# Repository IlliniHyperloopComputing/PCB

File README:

# Illini Hyperloop PCB

The shared development environment for the Illini Hyperloop PCB team. Contains all libraries and schematics for the electronics on the pod. 

## Getting Started

Obtain full student copy of Eagle. https://www.autodesk.com/education/free-software/eagle
Initialize repository in a Eagle folder. 
After youve got your git repository up and running youre going to want to configure eagle. Files included in the library folder arent enabled by default. Youre going to have to go through and make sure you select Use All for the subfolders provided so the little green dot appears to the right side next to libraries in the Control Panel.

### Prerequisites

Eagle 

## Authors

* **Matthew Klock** - *Team Lead* - [Matthew-Klock](https://github.com/Matthew-Klock)

See also the list of [contributors](https://github.com/your/project/contributors) who participated in this project.

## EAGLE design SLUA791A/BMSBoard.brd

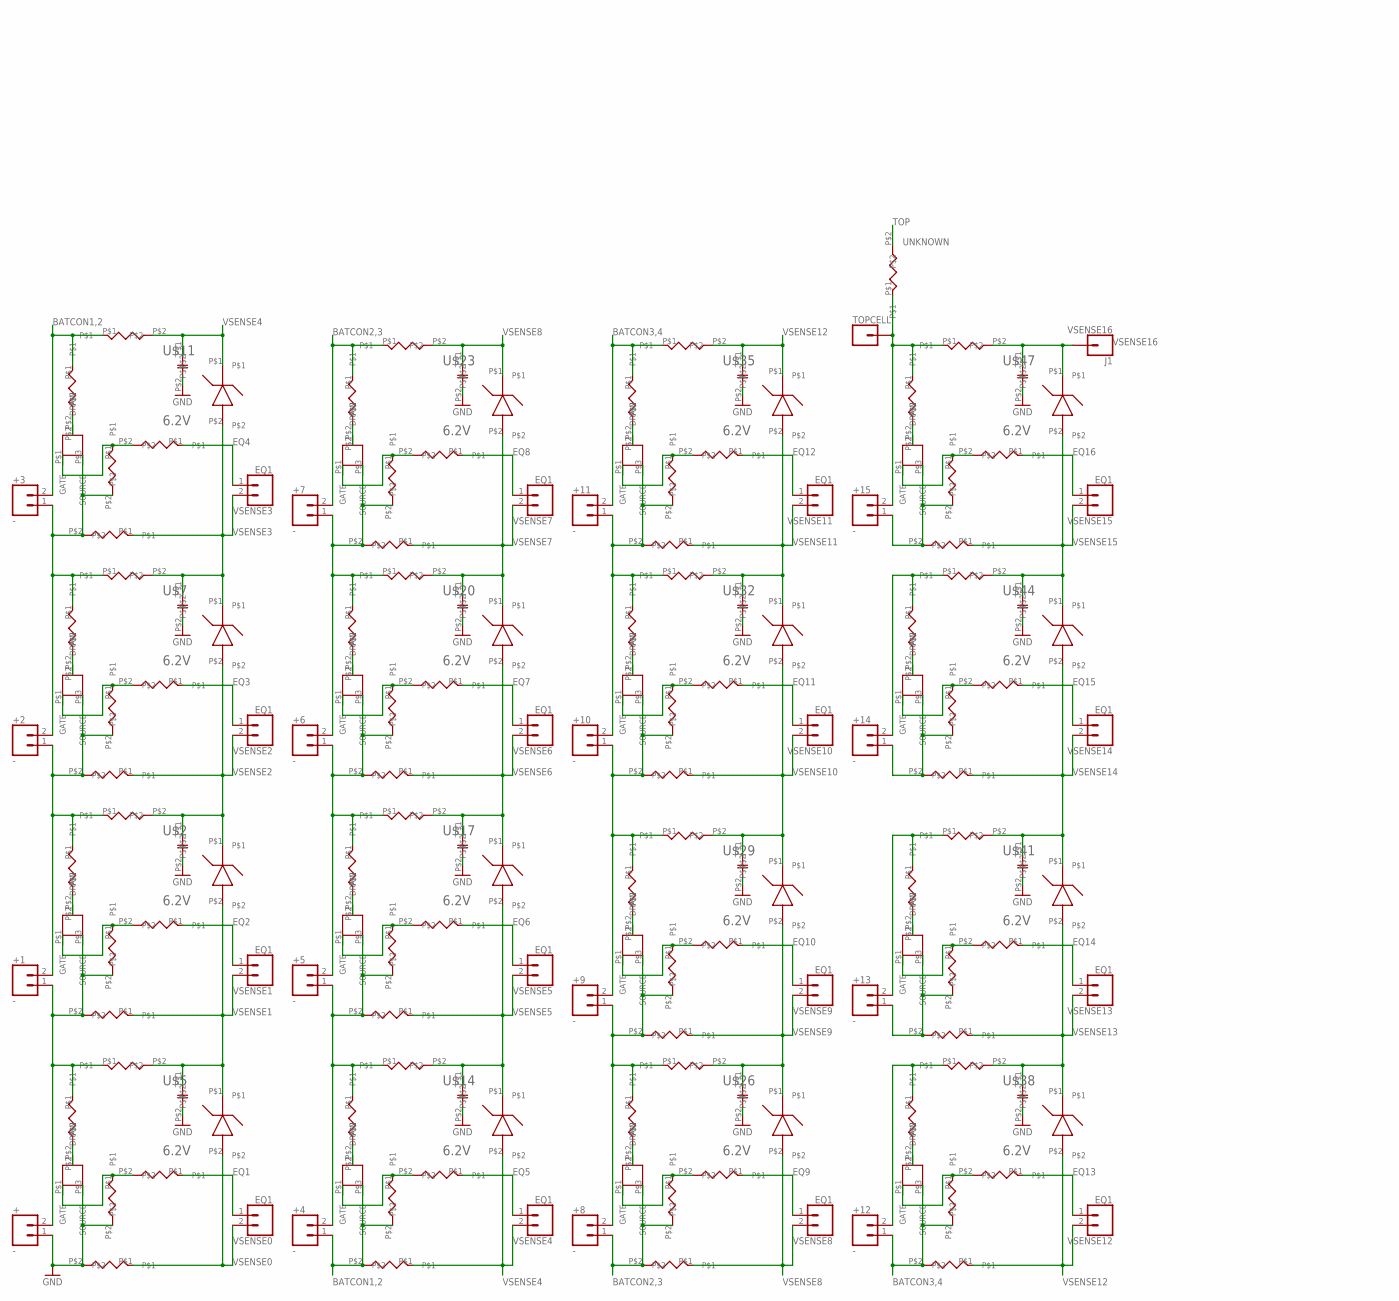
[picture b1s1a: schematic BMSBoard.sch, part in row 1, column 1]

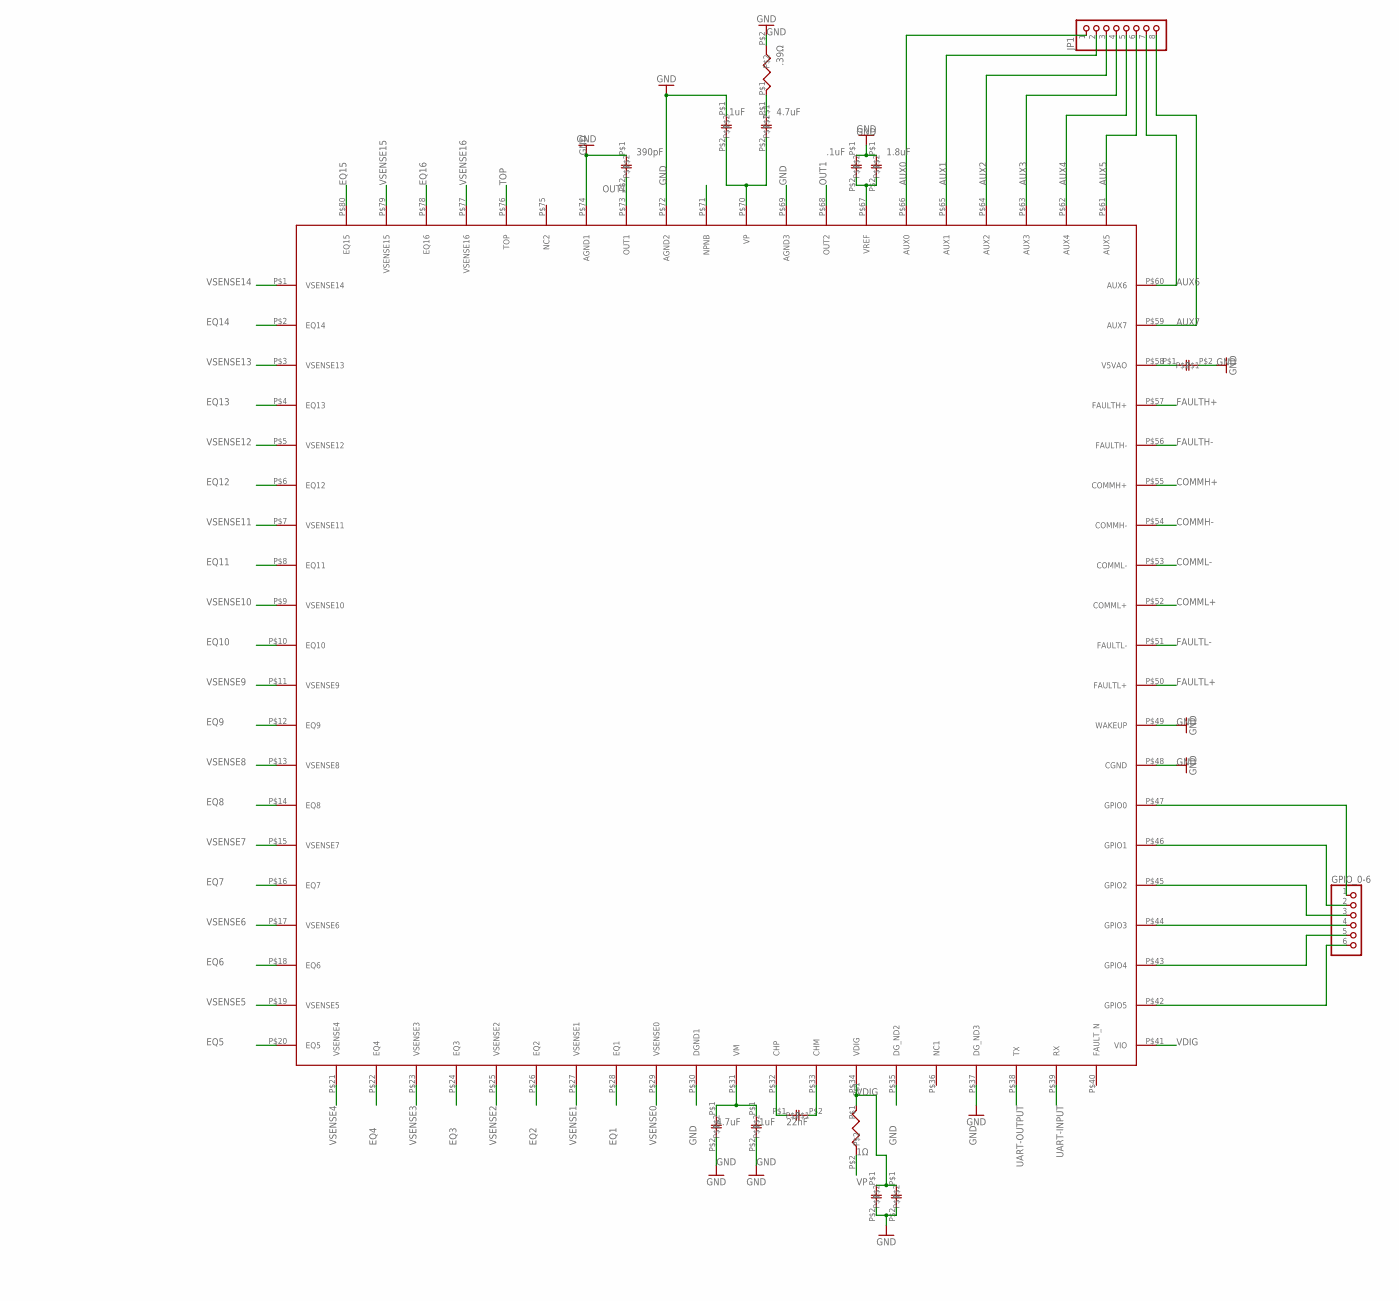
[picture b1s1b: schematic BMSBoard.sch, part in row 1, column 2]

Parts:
1UF, 1UF1, 1UF2, 1UF3, 1UF4, 1UF5, 1UF6, 1UF7, 1UF8, 1UF9, 1UF10, 1UF11, 1UF12, 1UF13, 1UF14, 1UF15: 1uF; CL21B105KBFNNNG
2KΩ, 2KΩ1, 2KΩ2, 2KΩ3, 2KΩ4, 2KΩ5, 2KΩ6, 2KΩ7, 2KΩ8, 2KΩ9, 2KΩ10, 2KΩ11, 2KΩ12, 2KΩ13, 2KΩ14, 2KΩ15: 2kΩ; PWR3014W1000JE
75Ω, 75Ω1, 75Ω2, 75Ω3, 75Ω4, 75Ω5, 75Ω6, 75Ω7, 75Ω8, 75Ω9, 75Ω10, 75Ω11, 75Ω12, 75Ω13, 75Ω14, 75Ω15: 75Ω; PWR3014W1000JE
100KΩ, 100KΩ1, 100KΩ2, 100KΩ3, 100KΩ4, 100KΩ5, 100KΩ6, 100KΩ7, 100KΩ8, 100KΩ9, 100KΩ10, 100KΩ11, 100KΩ12, 100KΩ13, 100KΩ14, 100KΩ15: 100kΩ; PWR3014W1000JE
100Ω, 100Ω1, 100Ω2, 100Ω3, 100Ω4, 100Ω5, 100Ω6, 100Ω7, 100Ω8, 100Ω9, 100Ω10, 100Ω11, 100Ω12, 100Ω13, 100Ω14, 100Ω15: 100Ω; PWR3014W1000JE
+, +1, +2, +3, +4, +5, +6, +7, +8, +9, +10, +11, +12, +13, +14, +15: -; 1X02
GPIO_0-6: PINHD-1X6; 1X06
J1: VSENSE16; 1X01
JP1: PINHD-1X8BIG; 1X08-BIG
TOPCELL: CONN_01; 1X01
U$1, U$4, U$6, U$10, U$13, U$16, U$19, U$22, U$25, U$28, U$31, U$34, U$37, U$40, U$43, U$46: 2V7002KT1G
U$2, U$5, U$7, U$11, U$14, U$17, U$20, U$23, U$26, U$29, U$32, U$35, U$38, U$41, U$44, U$47: 6.2V; SOD-123-2
U$3, U$8, U$9, U$12, U$15, U$18, U$21, U$24, U$27, U$30, U$33, U$36, U$39, U$42, U$45, U$48: 100Ω; PWR3014W1000JE
U$49: BQ76PL455A-Q1
U$50: 22nF; CL21B105KBFNNNG
U$51, U$52, U$54, U$55, U$56, U$57, U$58, U$59, U$60, U$61: CL21B105KBFNNNG
U$53: 1Ω; PWR3014W1000JE
U$62, U$63: PWR3014W1000JE
VSENSE0, VSENSE1, VSENSE2, VSENSE3, VSENSE4, VSENSE5, VSENSE6, VSENSE7, VSENSE8, VSENSE9, VSENSE10, VSENSE11, VSENSE12, VSENSE13, VSENSE14, VSENSE15: EQ1; 1X02

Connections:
AUX0: JP1.1, U$49.P$66 (AUX0)
AUX1: JP1.2, U$49.P$65 (AUX1)
AUX2: JP1.3, U$49.P$64 (AUX2)
AUX3: JP1.4, U$49.P$63 (AUX3)
AUX4: JP1.5, U$49.P$62 (AUX4)
AUX5: JP1.6, U$49.P$61 (AUX5)
AUX6: JP1.7, U$49.P$60 (AUX6)
AUX7: JP1.8, U$49.P$59 (AUX7)
BATCON1,2: 75Ω3.P$1, 100KΩ4.P$2, 100Ω4.P$2, +3.2, +4.1, U$12.P$1, U$13.P$3 (SOURCE)
BATCON2,3: 75Ω7.P$1, 100KΩ8.P$2, 100Ω8.P$2, +7.2, +8.1, U$24.P$1, U$25.P$3 (SOURCE)
BATCON3,4: 75Ω11.P$1, 100KΩ12.P$2, 100Ω12.P$2, +11.2, +12.1, U$36.P$1, U$37.P$3 (SOURCE)
COMMH+: U$49.P$55 (COMMH+)
COMMH-: U$49.P$54 (COMMH-)
COMML+: U$49.P$52 (COMML+)
COMML-: U$49.P$53 (COMML-)
EQ1: 2KΩ.P$1, U$49.P$28 (EQ1), VSENSE0.1
EQ2: 2KΩ1.P$1, U$49.P$26 (EQ2), VSENSE1.1
EQ3: 2KΩ2.P$1, U$49.P$24 (EQ3), VSENSE2.1
EQ4: 2KΩ3.P$1, U$49.P$22 (EQ4), VSENSE3.1
EQ5: 2KΩ4.P$1, U$49.P$20 (EQ5), VSENSE4.1
EQ6: 2KΩ5.P$1, U$49.P$18 (EQ6), VSENSE5.1
EQ7: 2KΩ6.P$1, U$49.P$16 (EQ7), VSENSE6.1
EQ8: 2KΩ7.P$1, U$49.P$14 (EQ8), VSENSE7.1
EQ9: 2KΩ8.P$1, U$49.P$12 (EQ9), VSENSE8.1
EQ10: 2KΩ9.P$1, U$49.P$10 (EQ10), VSENSE9.1
EQ11: 2KΩ10.P$1, U$49.P$8 (EQ11), VSENSE10.1
EQ12: 2KΩ11.P$1, U$49.P$6 (EQ12), VSENSE11.1
EQ13: 2KΩ12.P$1, U$49.P$4 (EQ13), VSENSE12.1
EQ14: 2KΩ13.P$1, U$49.P$2 (EQ14), VSENSE13.1
EQ15: 2KΩ14.P$1, U$49.P$80 (EQ15), VSENSE14.1
EQ16: 2KΩ15.P$1, U$49.P$78 (EQ16), VSENSE15.1
FAULTH+: U$49.P$57 (FAULTH+)
FAULTH-: U$49.P$56 (FAULTH-)
FAULTL+: U$49.P$50 (FAULTL+)
FAULTL-: U$49.P$51 (FAULTL-)
GND: 1UF.P$2, 1UF1.P$2, 1UF2.P$2, 1UF3.P$2, 1UF4.P$2, 1UF5.P$2, 1UF6.P$2, 1UF7.P$2, 1UF8.P$2, 1UF9.P$2, 1UF10.P$2, 1UF11.P$2, 1UF12.P$2, 1UF13.P$2, 1UF14.P$2, 1UF15.P$2, 100KΩ.P$2, 100Ω.P$2, +.1, U$4.P$3 (SOURCE), U$49.P$30 (DGND1), U$49.P$35 (DG_ND2), U$49.P$37 (DG_ND3), U$49.P$48 (CGND), U$49.P$49 (WAKEUP), U$49.P$69 (AGND3), U$49.P$72 (AGND2), U$49.P$74 (AGND1), U$51.P$2, U$52.P$2, U$54.P$2, U$55.P$2, U$56.P$2, U$57.P$1, U$58.P$1, U$59.P$1, U$60.P$1, U$62.P$2
unnamed: 2KΩ.P$2, 100KΩ.P$1, U$4.P$1 (GATE)
unnamed: U$61.P$1, U$62.P$1
unnamed: 75Ω.P$2, U$4.P$2 (DRAIN)
unnamed: 75Ω.P$1, 100KΩ1.P$2, 100Ω1.P$2, +.2, +1.1, U$1.P$3 (SOURCE), U$8.P$1
unnamed: 75Ω2.P$1, 100KΩ3.P$2, 100Ω3.P$2, +2.2, +3.1, U$9.P$1, U$10.P$3 (SOURCE)
unnamed: 2KΩ1.P$2, 100KΩ1.P$1, U$1.P$1 (GATE)
unnamed: 75Ω1.P$2, U$1.P$2 (DRAIN)
unnamed: 75Ω1.P$1, 100KΩ2.P$2, 100Ω2.P$2, +1.2, +2.1, U$3.P$1, U$6.P$3 (SOURCE)
unnamed: 2KΩ2.P$2, 100KΩ2.P$1, U$6.P$1 (GATE)
unnamed: 75Ω2.P$2, U$6.P$2 (DRAIN)
unnamed: 2KΩ3.P$2, 100KΩ3.P$1, U$10.P$1 (GATE)
unnamed: 75Ω3.P$2, U$10.P$2 (DRAIN)
unnamed: 2KΩ4.P$2, 100KΩ4.P$1, U$13.P$1 (GATE)
unnamed: 75Ω4.P$2, U$13.P$2 (DRAIN)
unnamed: 2KΩ5.P$2, 100KΩ5.P$1, U$16.P$1 (GATE)
unnamed: 75Ω5.P$2, U$16.P$2 (DRAIN)
unnamed: 75Ω5.P$1, 100KΩ6.P$2, 100Ω6.P$2, +5.2, +6.1, U$18.P$1, U$19.P$3 (SOURCE)
unnamed: 2KΩ6.P$2, 100KΩ6.P$1, U$19.P$1 (GATE)
unnamed: 75Ω6.P$2, U$19.P$2 (DRAIN)
unnamed: 2KΩ7.P$2, 100KΩ7.P$1, U$22.P$1 (GATE)
unnamed: 75Ω7.P$2, U$22.P$2 (DRAIN)
unnamed: 2KΩ8.P$2, 100KΩ8.P$1, U$25.P$1 (GATE)
unnamed: 75Ω8.P$2, U$25.P$2 (DRAIN)
unnamed: 75Ω8.P$1, 100KΩ9.P$2, 100Ω9.P$2, +8.2, +9.1, U$27.P$1, U$28.P$3 (SOURCE)
unnamed: 2KΩ9.P$2, 100KΩ9.P$1, U$28.P$1 (GATE)
unnamed: 75Ω9.P$2, U$28.P$2 (DRAIN)
unnamed: 75Ω9.P$1, 100KΩ10.P$2, 100Ω10.P$2, +9.2, +10.1, U$30.P$1, U$31.P$3 (SOURCE)
unnamed: 2KΩ10.P$2, 100KΩ10.P$1, U$31.P$1 (GATE)
unnamed: 75Ω10.P$2, U$31.P$2 (DRAIN)
unnamed: 2KΩ11.P$2, 100KΩ11.P$1, U$34.P$1 (GATE)
unnamed: 75Ω11.P$2, U$34.P$2 (DRAIN)
unnamed: 2KΩ12.P$2, 100KΩ12.P$1, U$37.P$1 (GATE)
unnamed: 75Ω12.P$2, U$37.P$2 (DRAIN)
unnamed: 75Ω12.P$1, +12.2, U$39.P$1
unnamed: 2KΩ13.P$2, 100KΩ13.P$1, U$40.P$1 (GATE)
unnamed: 75Ω13.P$2, U$40.P$2 (DRAIN)
unnamed: 75Ω13.P$1, +13.2, U$42.P$1
unnamed: 2KΩ14.P$2, 100KΩ14.P$1, U$43.P$1 (GATE)
unnamed: 75Ω14.P$2, U$43.P$2 (DRAIN)
unnamed: 75Ω14.P$1, +14.2, U$45.P$1
unnamed: 2KΩ15.P$2, 100KΩ15.P$1, U$46.P$1 (GATE)
unnamed: 75Ω15.P$2, U$46.P$2 (DRAIN)
unnamed: 75Ω15.P$1, +15.2, TOPCELL.1, U$48.P$1, U$63.P$1
unnamed: 75Ω4.P$1, 100KΩ5.P$2, 100Ω5.P$2, +4.2, +5.1, U$15.P$1, U$16.P$3 (SOURCE)
unnamed: 75Ω6.P$1, 100KΩ7.P$2, 100Ω7.P$2, +6.2, +7.1, U$21.P$1, U$22.P$3 (SOURCE)
unnamed: 75Ω10.P$1, 100KΩ11.P$2, 100Ω11.P$2, +10.2, +11.1, U$33.P$1, U$34.P$3 (SOURCE)
unnamed: 100KΩ13.P$2, 100Ω13.P$2, +13.1, U$40.P$3 (SOURCE)
unnamed: 100KΩ14.P$2, 100Ω14.P$2, +14.1, U$43.P$3 (SOURCE)
unnamed: 100KΩ15.P$2, 100Ω15.P$2, +15.1, U$46.P$3 (SOURCE)
unnamed: U$49.P$31 (VM), U$51.P$1, U$52.P$1
unnamed: U$49.P$32 (CHP), U$50.P$1
unnamed: U$49.P$33 (CHM), U$50.P$2
unnamed: GPIO_0-6.6, U$49.P$42 (GPIO5)
unnamed: GPIO_0-6.5, U$49.P$43 (GPIO4)
unnamed: GPIO_0-6.4, U$49.P$44 (GPIO3)
unnamed: GPIO_0-6.3, U$49.P$45 (GPIO2)
unnamed: GPIO_0-6.2, U$49.P$46 (GPIO1)
unnamed: GPIO_0-6.1, U$49.P$47 (GPIO0)
unnamed: U$49.P$58 (V5VAO), U$56.P$1
unnamed: U$49.P$70 (VP), U$60.P$2, U$61.P$2
OUT1: U$49.P$68 (OUT2), U$49.P$73 (OUT1), U$59.P$2
TOP: U$49.P$76 (TOP), U$63.P$2
UART-INPUT: U$49.P$39 (RX)
UART-OUTPUT: U$49.P$38 (TX)
VDIG: U$49.P$34 (VDIG), U$49.P$41 (VIO), U$53.P$1, U$54.P$1, U$55.P$1
VP: U$53.P$2
VREF: U$49.P$67 (VREF), U$57.P$2, U$58.P$2
VSENSE0: 100Ω.P$1, U$5.P$2, U$49.P$29 (VSENSE0), VSENSE0.2
VSENSE1: 1UF.P$1, 100Ω1.P$1, U$2.P$2, U$5.P$1, U$8.P$2, U$49.P$27 (VSENSE1), VSENSE1.2
VSENSE2: 1UF1.P$1, 100Ω2.P$1, U$2.P$1, U$3.P$2, U$7.P$2, U$49.P$25 (VSENSE2), VSENSE2.2
VSENSE3: 1UF2.P$1, 100Ω3.P$1, U$7.P$1, U$9.P$2, U$11.P$2, U$49.P$23 (VSENSE3), VSENSE3.2
VSENSE4: 1UF3.P$1, 100Ω4.P$1, U$11.P$1, U$12.P$2, U$14.P$2, U$49.P$21 (VSENSE4), VSENSE4.2
VSENSE5: 1UF4.P$1, 100Ω5.P$1, U$14.P$1, U$15.P$2, U$17.P$2, U$49.P$19 (VSENSE5), VSENSE5.2
VSENSE6: 1UF5.P$1, 100Ω6.P$1, U$17.P$1, U$18.P$2, U$20.P$2, U$49.P$17 (VSENSE6), VSENSE6.2
VSENSE7: 1UF6.P$1, 100Ω7.P$1, U$20.P$1, U$21.P$2, U$23.P$2, U$49.P$15 (VSENSE7), VSENSE7.2
VSENSE8: 1UF7.P$1, 100Ω8.P$1, U$23.P$1, U$24.P$2, U$26.P$2, U$49.P$13 (VSENSE8), VSENSE8.2
VSENSE9: 1UF8.P$1, 100Ω9.P$1, U$26.P$1, U$27.P$2, U$29.P$2, U$49.P$11 (VSENSE9), VSENSE9.2
VSENSE10: 1UF9.P$1, 100Ω10.P$1, U$29.P$1, U$30.P$2, U$32.P$2, U$49.P$9 (VSENSE10), VSENSE10.2
VSENSE11: 1UF10.P$1, 100Ω11.P$1, U$32.P$1, U$33.P$2, U$35.P$2, U$49.P$7 (VSENSE11), VSENSE11.2
VSENSE12: 1UF11.P$1, 100Ω12.P$1, U$35.P$1, U$36.P$2, U$38.P$2, U$49.P$5 (VSENSE12), VSENSE12.2
VSENSE13: 1UF12.P$1, 100Ω13.P$1, U$38.P$1, U$39.P$2, U$41.P$2, U$49.P$3 (VSENSE13), VSENSE13.2
VSENSE14: 1UF13.P$1, 100Ω14.P$1, U$41.P$1, U$42.P$2, U$44.P$2, U$49.P$1 (VSENSE14), VSENSE14.2
VSENSE15: 1UF14.P$1, 100Ω15.P$1, U$44.P$1, U$45.P$2, U$47.P$2, U$49.P$79 (VSENSE15), VSENSE15.2
VSENSE16: 1UF15.P$1, J1.1, U$47.P$1, U$48.P$2, U$49.P$77 (VSENSE16)

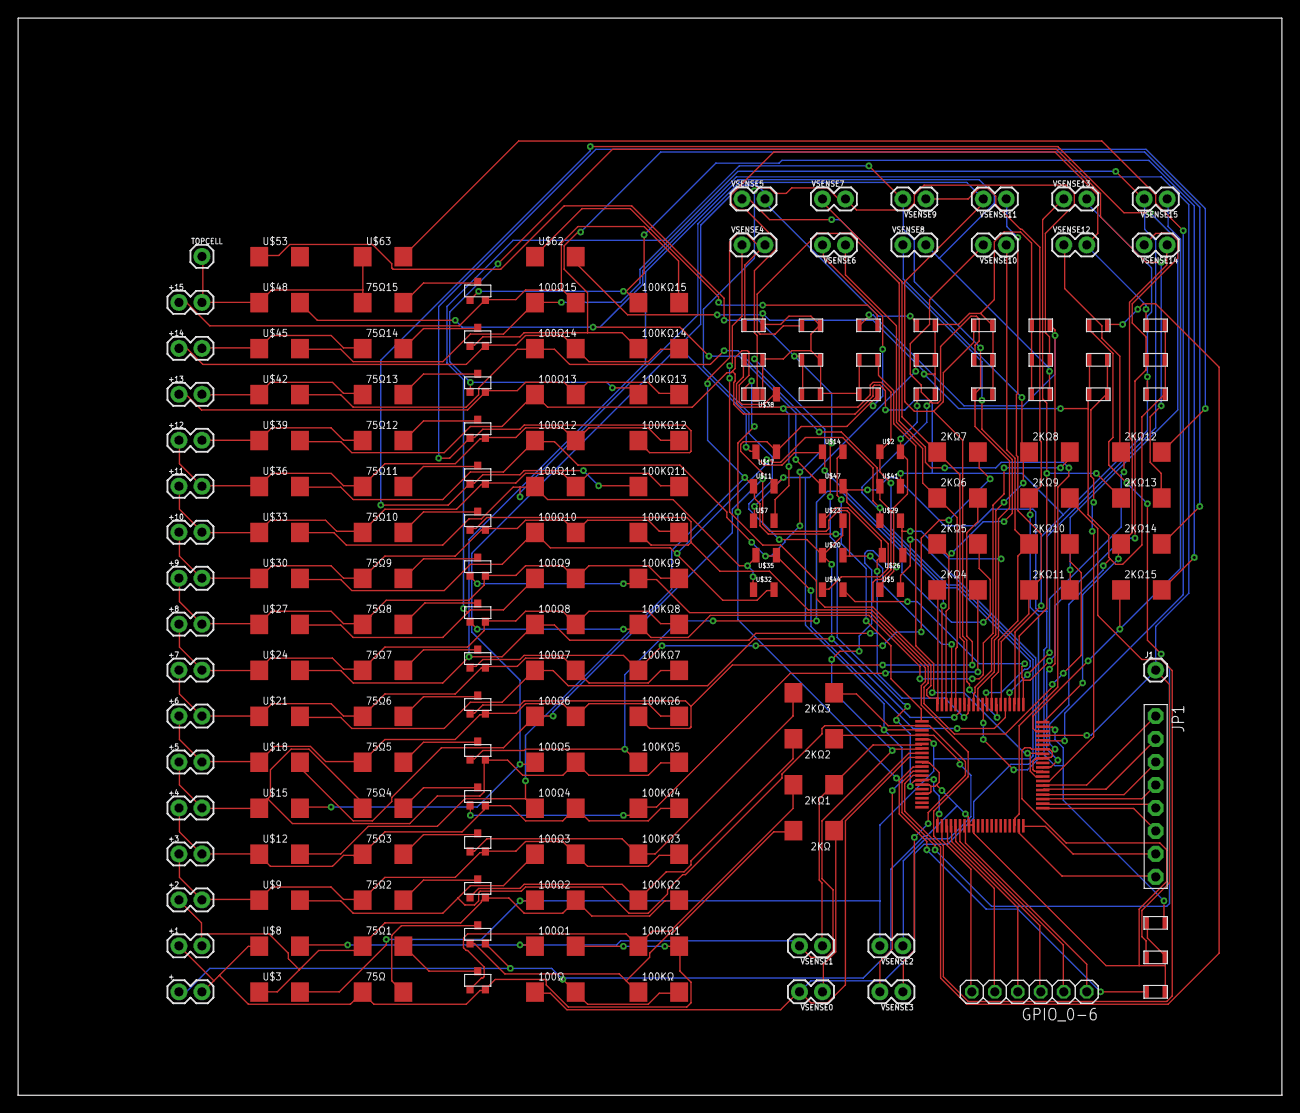
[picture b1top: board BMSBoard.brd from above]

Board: 2 copper layers, 139.7 x 119.0 mm, 179 parts (0 on the bottom side), 109 nets.

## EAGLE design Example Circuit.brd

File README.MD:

# Illini Hyperloop PCB

The shared development environment for the Illini Hyperloop PCB team. Contains all libraries and schematics for the electronics on the pod. 

## Repo layout:
1. Default branch is `pod4`, and pull requests must be made to merge into it
2. `master` branch will only be used for correct, working code. A pull request must be made to merge

## Getting Started

1. [Obtain full student copy of Eagle.](https://www.autodesk.com/education/free-software/eagle)
2. Clone this Repo: `git clone https://github.com/IlliniHyperloopComputing/PCB` 
3. Move inside the `PCB` folder that was just created. 
4. Run `git checkout -b *YOUR-NAME* `. This creates a branch for you to work on
5. Add the respective paths to libraries, boards, etc in EAGLE (Options>Directories).
6. Make your updates/ changes
7. `git status` to view changes, and use `git add *file* ` to add files, and then `git commit -m "your-message"`. 
8. `git push origin *YOUR-NAME* `. If there is an issue, do what `git` suggests you run, or it might be because you are not a member of our GitHub organization (Contact us).

### Prerequisites

* Eagle 

## Pull Requests
* Write a short description of what you did for the request.
* Please add your devices to Hyperloop-Library/Pod4.lbr, do not make them their own library.

## Authors

* **Matthew-Klock** - *Team Lead* - [Matthew Klock](https://github.com/Matthew-Klock)

See also the list of [team members](https://github.com/orgs/IlliniHyperloopComputing/teams/pcb-team) who participated in this project.

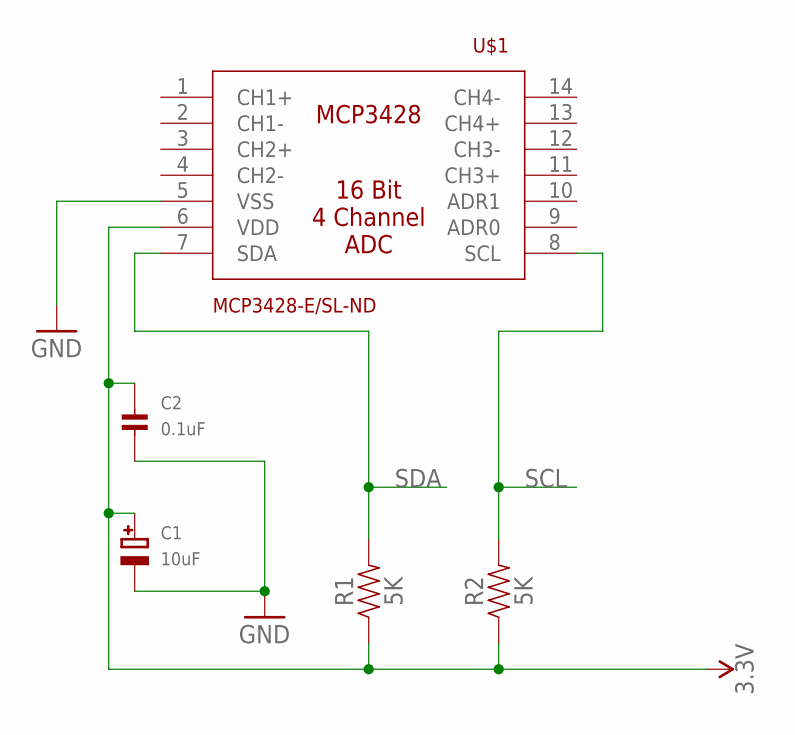
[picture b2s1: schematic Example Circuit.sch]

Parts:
C1: 10uF; EIA3216-18/A-R
C2: 0.1uF; 0603
R1, R2: 5K; 0603
U$1: MCP3428-E/SL-ND; 14SOIC

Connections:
3.3V: C1.+, C2.1, R1.1, R2.1, U$1.6 (VDD)
GND: C1.-, C2.2, U$1.5 (VSS)
SCL: R2.2, U$1.8 (SCL)
SDA: R1.2, U$1.7 (SDA)

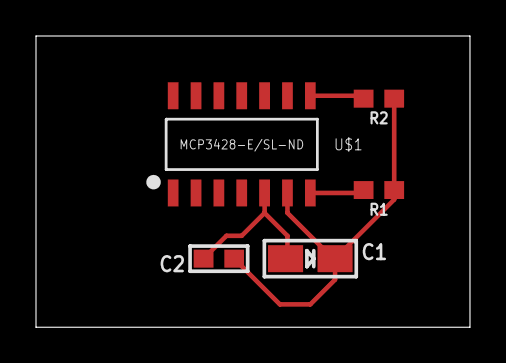
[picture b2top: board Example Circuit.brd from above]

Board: 2 copper layers, 24.1 x 16.2 mm, 5 parts (0 on the bottom side), 4 nets.

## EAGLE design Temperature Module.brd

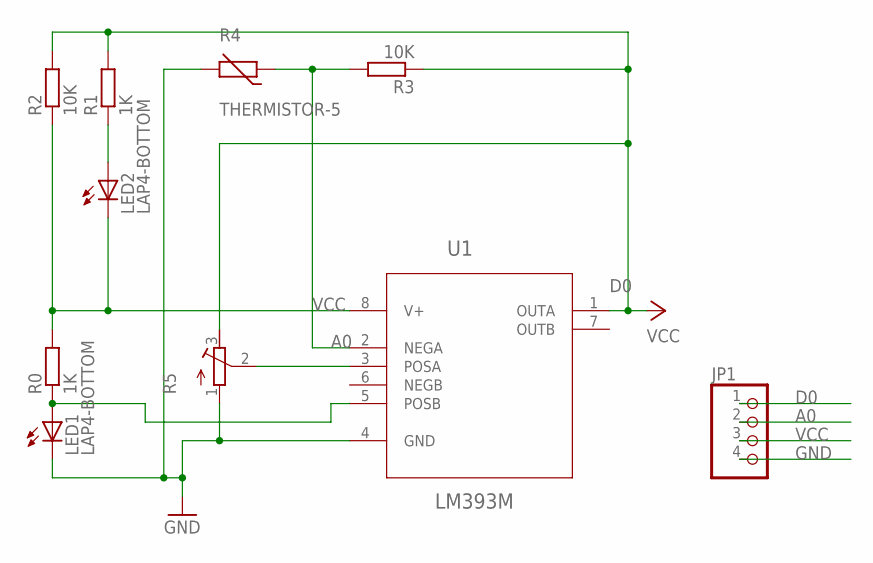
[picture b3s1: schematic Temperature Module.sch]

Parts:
JP1: PINHD-1X4; 1X04
LED1, LED2: LAP4-BOTTOM; P47F-BOTTOM
R0, R1: 1K; MINI_MELF-0207R
R2, R3: 10K; MINI_MELF-0207R
R4: THERMISTOR-5; R-5
R5: R-TRIMMCVR42A; RTRIMCVR42A
U1: LM393M; SOIC127P620X175-8N

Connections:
A0: JP1.2, R3.2, R4.1, U1.2 (NEGA)
D0: JP1.1, R1.2, R2.2, R3.1, R5.3 (E), U1.1 (OUTA)
GND: JP1.4, LED1.C, R4.2, R5.1 (A), U1.4 (GND)
unnamed: R5.2 (S), U1.3 (POSA)
unnamed: LED1.A, R0.1, U1.5 (POSB)
unnamed: LED2.A, R1.1
VCC: JP1.3, LED2.C, R0.2, R2.1, U1.8 (V+)

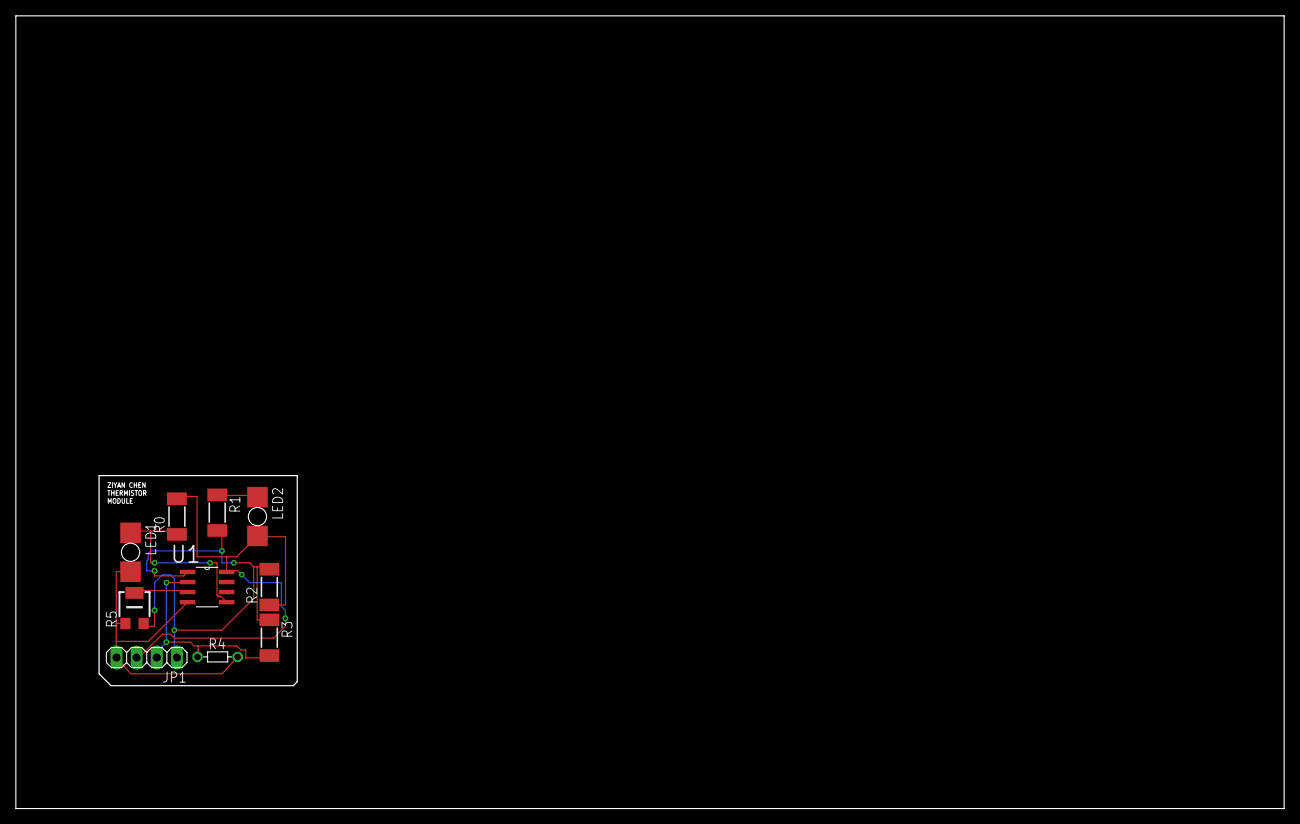
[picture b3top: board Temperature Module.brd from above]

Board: 2 copper layers, 160.0 x 100.0 mm, 10 parts (0 on the bottom side), 7 nets.

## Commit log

2018-09-22 test
2018-09-23 added base library
2018-09-23 added VG32 (rand part)
2018-09-26 Temperature Module
2018-09-26 Temperature Module Board Design
2018-09-26 MXC6255XC accelerometer
2018-09-26 Revert "MXC6255XC accelerometer"
2018-09-26 accelerometerMXC6255XC
2018-09-26 deletewrongfile
2018-09-26 fixfilelocation
2018-09-26 Gene lee (#8)
    Added MXC6255XC accelerometer to the pod4 library
2018-09-26 fixedsmd
2018-09-26 Gene lee (#10)
    Changed Pads to SMD
2018-09-27 ADC Library
2018-10-04 Pod4 Library with LIS3DH
2018-10-07 Thermistor NTCLE100E3
    I add the NTCLE100E3 part to the repository
2018-10-07 Added part to library
2018-10-11 Pod4 Library with LIS3DH (#12)
2018-10-12 added origin point
2018-10-12 merged with the main library
2018-10-12 NTCLE100E3 (#14)
    Added NTCLE100E3 Thermistor
2018-10-19 resolved issues
2018-12-05 added dq76
2018-12-05 Added dq76 (#17)
    * added dq76
2018-12-05 fixed it
2018-12-05 added zener diode
2018-12-05 add resistor
2018-12-07 made the chip bigger
2018-12-07 Soham karanjikar (#19)
    * fixed it
    * added zener diode
    * add resistor
    * made the chip bigger
2019-02-01 Added 2V7002KT1G
2019-02-01 Changed size of MOSFET Schematic
2019-02-01 resistors
2019-02-01 resistors (#21)
2019-02-08 Patrick shalton patch 1 (#20)
    * Pod4 Library with LIS3DH
    * Added 2V7002KT1G
2019-02-08 Deleted Everything
2019-02-08 Added BMSBoard
2019-02-15 Added BMS Schematic
2019-02-22 Updated BMSBoard
2019-02-27 add board layout
2019-03-01 Updated library
2019-03-01 Add BMSBoard new design layout

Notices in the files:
parts and their libraries:
microbuilder: This work is placed in the public domain, and may be freely used for commercial and non-commercial work with the following conditions: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
SparkFun-Resistors: Licensing: Creative Commons ShareAlike 4.0 International - https://creativecommons.org/licenses/by-sa/4.0
